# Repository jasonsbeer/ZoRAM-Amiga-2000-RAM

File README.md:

# ZoRAM - Eight Megabyte Fast RAM Expansion for the Amiga 2000

This project does not work at this time. Build at your own risk.

I have always felt big box Amiga's should be used as intended. Expansion should be targeted to the expansion slots provided. This project aims to provde an 8 megabyte expansion option via the Zorro II bus of the Amiga 2000. Based on LIV2's GottaGoFastRAM for 68000 DIP based Amigas. Due to the relative messiness of the  data and address line locations on the Zorro II connector, it was necessary to  change the connection points on the Xilinx. As such, the JED file for this project is specific to this project and cannot be interchanged with LIV2's original.

# PCB Ordering and Assembly

Under construction

# Programming the CPLD

To be completed later.

# BOM

|Component|Package|Location|QTY|Source|Part Number|
--- | --- | --- | --- | --- | ---
4Mx16 DRAM|TSOP(II)| U6 | 1 | Ali Express or E-Bay| K4E641612D or GM71VS65163
XC9572XL-10VQ64C|64-VQFP|U5|1|DigiKey|122-1266-ND or 122-1982-ND
AP2210N-3.3TRG1|SOT-23-3|U2|1|DigiKey|AP2210N-3.3TRG1DICT-ND
SN74LVC245A|SOIC|U3,U4|2|DigiKey|296-1232-1-ND
Ferrite Bead (600 Ohms@100MHz)|1206|FB1|1|DigiKey|MH3261-601YCT-ND
0.1uF Ceramic Capacitor|1206|C3-12|10|DigiKey|1276-2744-1-ND
4.7uF Ceramic Capacitor|1206|C1|1|DigiKey|1276-1055-1-ND
10uF Ceramic Capacitor|1206|C2|1|DigiKey|1276-1853-1-ND
6 Pin Male 2.54 Pitch Header (Optional)|--|J1|1|DigiKey|1849-PR20206VBNN-ND‎

# Revision History

V0.5 - Prototype Revision

V0.6 - Added missing trace between U3 pin 1 and U4 pin 1

V0.7 - Added ground planes

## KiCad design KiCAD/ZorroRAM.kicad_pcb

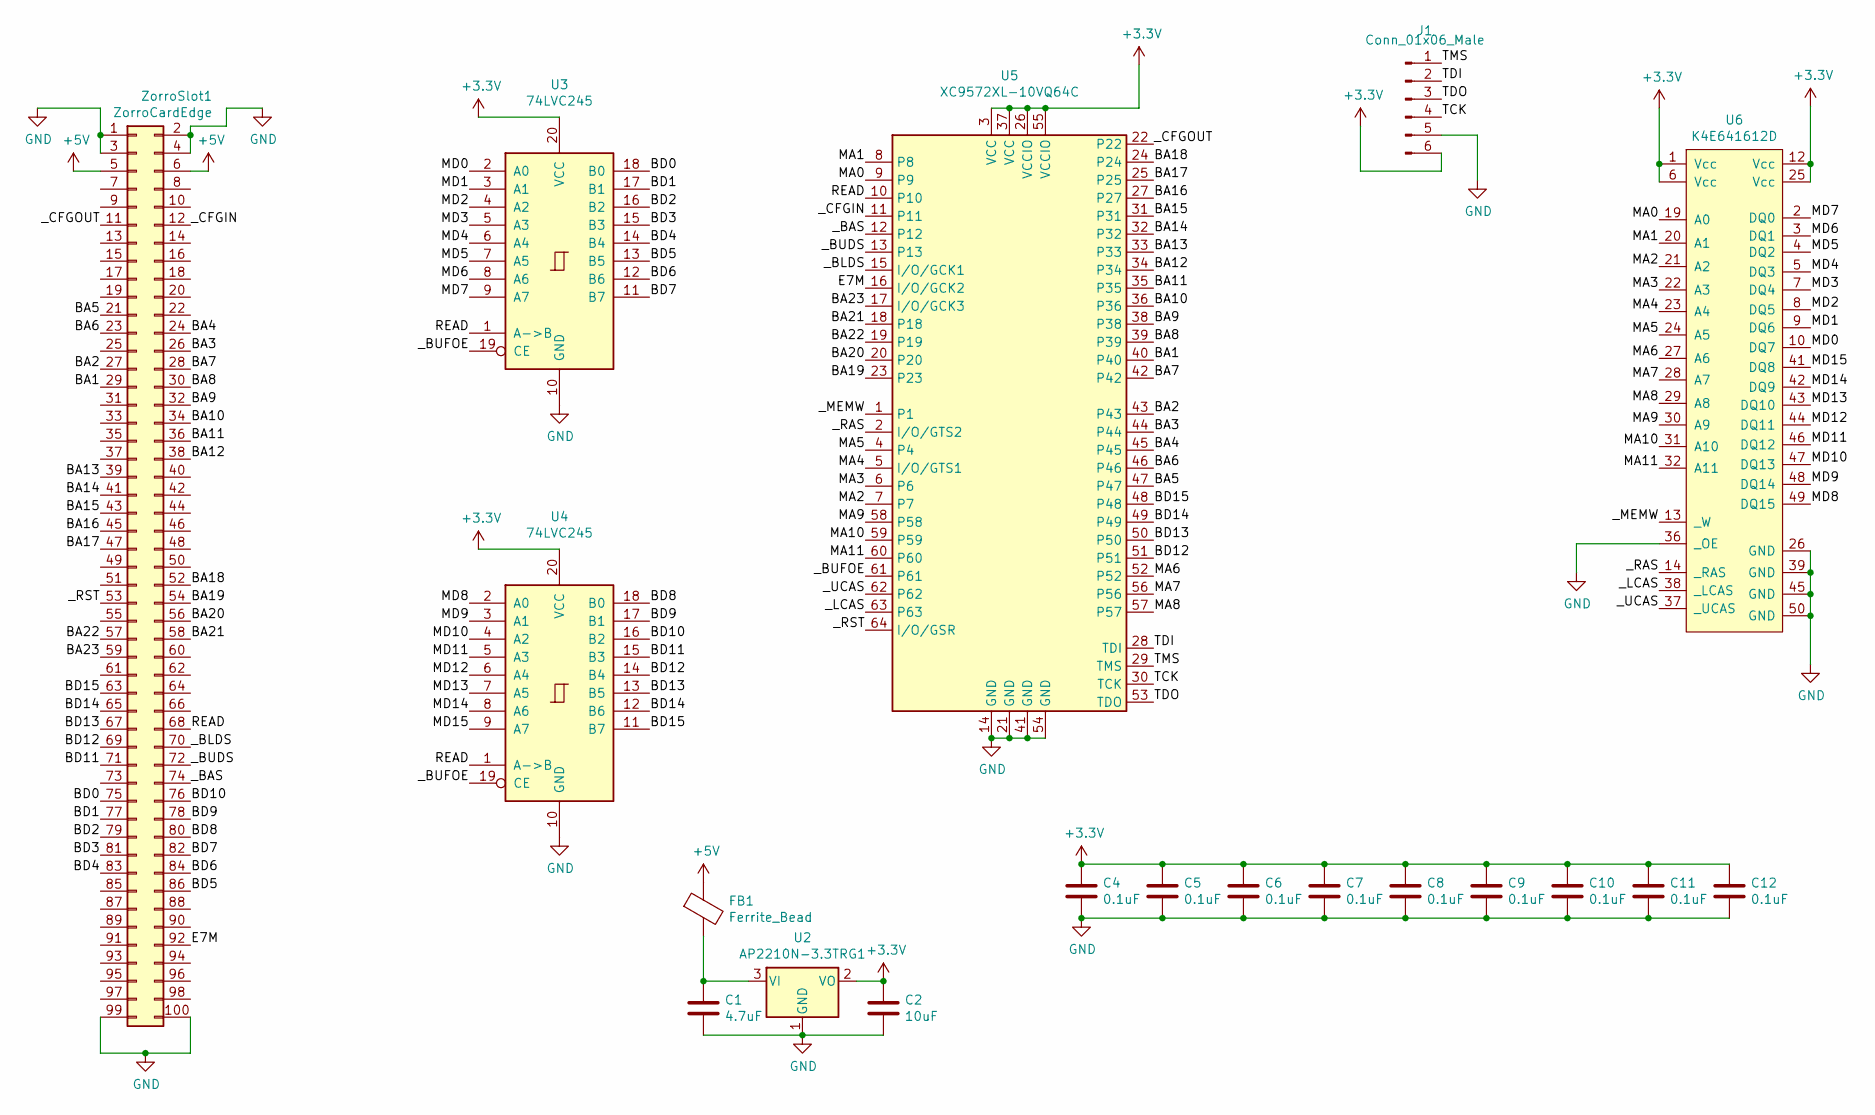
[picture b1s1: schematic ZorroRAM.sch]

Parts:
C1: 4.7uF; C_1206_3216Metric
C2: 10uF; C_1206_3216Metric
C4, C5, C6, C7, C8, C9, C10, C11, C12: 0.1uF; C_1206_3216Metric
FB1: Ferrite_Bead; C_1206_3216Metric
J1: Conn_01x06_Male; PinHeader_1x06_P2.54mm_Vertical
U2: AP2210N-3.3TRG1; SOT-23
U3, U4: 74LVC245; SOIC-20W_7.5x12.8mm_P1.27mm
U5: XC9572XL-10VQ64C; TQFP-64_10x10mm_P0.5mm
U6: K4E641612D; TSOP-II-50_P0.8mm
ZorroSlot1: ZorroCardEdge

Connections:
+3V3: C2.1, C4.1, C5.1, C6.1, C7.1, C8.1, C9.1, C10.1, C11.1, C12.1, J1.6, U2.2 (VO), U3.20 (VCC), U4.20 (VCC), U5.3 (VCC), U5.26 (VCCIO), U5.37 (VCC), U5.55 (VCCIO), U6.1 (Vcc), U6.6 (Vcc), U6.12 (Vcc), U6.25 (Vcc)
+5V: FB1.1, ZorroSlot1.5, ZorroSlot1.6
/BA1: U5.40, ZorroSlot1.29
/BA2: U5.43, ZorroSlot1.27
/BA3: U5.44, ZorroSlot1.26
/BA4: U5.45, ZorroSlot1.24
/BA5: U5.47, ZorroSlot1.21
/BA6: U5.46, ZorroSlot1.23
/BA7: U5.42, ZorroSlot1.28
/BA8: U5.39, ZorroSlot1.30
/BA9: U5.38, ZorroSlot1.32
/BA10: U5.36, ZorroSlot1.34
/BA11: U5.35, ZorroSlot1.36
/BA12: U5.34, ZorroSlot1.38
/BA13: U5.33, ZorroSlot1.39
/BA14: U5.32, ZorroSlot1.41
/BA15: U5.31, ZorroSlot1.43
/BA16: U5.27, ZorroSlot1.45
/BA17: U5.25, ZorroSlot1.47
/BA18: U5.24, ZorroSlot1.52
/BA19: U5.23, ZorroSlot1.54
/BA20: U5.20, ZorroSlot1.56
/BA21: U5.18, ZorroSlot1.58
/BA22: U5.19, ZorroSlot1.57
/BA23: U5.17 (I/O/GCK3), ZorroSlot1.59
/BD0: U3.18 (B0), ZorroSlot1.75
/BD1: U3.17 (B1), ZorroSlot1.77 (Pin77)
/BD2: U3.16 (B2), ZorroSlot1.79 (Pin79)
/BD3: U3.15 (B3), ZorroSlot1.81 (Pin81)
/BD4: U3.14 (B4), ZorroSlot1.83 (Pin83)
/BD5: U3.13 (B5), ZorroSlot1.86 (Pin86)
/BD6: U3.12 (B6), ZorroSlot1.84 (Pin84)
/BD7: U3.11 (B7), ZorroSlot1.82 (Pin82)
/BD8: U4.18 (B0), ZorroSlot1.80 (Pin80)
/BD9: U4.17 (B1), ZorroSlot1.78 (Pin78)
/BD10: U4.16 (B2), ZorroSlot1.76 (Pin76)
/BD11: U4.15 (B3), ZorroSlot1.71
/BD12: U4.14 (B4), U5.51, ZorroSlot1.69
/BD13: U4.13 (B5), U5.50, ZorroSlot1.67
/BD14: U4.12 (B6), U5.49, ZorroSlot1.65
/BD15: U4.11 (B7), U5.48, ZorroSlot1.63
/E7M: U5.16 (I/O/GCK2), ZorroSlot1.92 (Pin92)
/MA0: U5.9, U6.19 (A0)
/MA1: U5.8, U6.20 (A1)
/MA2: U5.7, U6.21 (A2)
/MA3: U5.6, U6.22 (A3)
/MA4: U5.5 (I/O/GTS1), U6.23 (A4)
/MA5: U5.4, U6.24 (A5)
/MA6: U5.52, U6.27 (A6)
/MA7: U5.56, U6.28 (A7)
/MA8: U5.57, U6.29 (A8)
/MA9: U5.58, U6.30 (A9)
/MA10: U5.59, U6.31 (A10)
/MA11: U5.60, U6.32 (A11)
/MD0: U3.2 (A0), U6.10 (DQ7)
/MD1: U3.3 (A1), U6.9 (DQ6)
/MD2: U3.4 (A2), U6.8 (DQ5)
/MD3: U3.5 (A3), U6.7 (DQ4)
/MD4: U3.6 (A4), U6.5 (DQ3)
/MD5: U3.7 (A5), U6.4 (DQ2)
/MD6: U3.8 (A6), U6.3 (DQ1)
/MD7: U3.9 (A7), U6.2 (DQ0)
/MD8: U4.2 (A0), U6.49 (DQ15)
/MD9: U4.3 (A1), U6.48 (DQ14)
/MD10: U4.4 (A2), U6.47 (DQ13)
/MD11: U4.5 (A3), U6.46 (DQ12)
/MD12: U4.6 (A4), U6.44 (DQ11)
/MD13: U4.7 (A5), U6.43 (DQ10)
/MD14: U4.8 (A6), U6.42 (DQ9)
/MD15: U4.9 (A7), U6.41 (DQ8)
/READ: U3.1 (A->B), U4.1 (A->B), U5.10, ZorroSlot1.68
/TCK: J1.4, U5.30 (TCK)
/TDI: J1.2, U5.28 (TDI)
/TDO: J1.3, U5.53 (TDO)
/TMS: J1.1, U5.29 (TMS)
/_BAS: U5.12, ZorroSlot1.74
/_BLDS: U5.15 (I/O/GCK1), ZorroSlot1.70
/_BUDS: U5.13, ZorroSlot1.72 (_BUDS)
/_BUFOE: U3.19 (CE), U4.19 (CE), U5.61
/_CFGIN: U5.11, ZorroSlot1.12
/_CFGOUT: U5.22, ZorroSlot1.11
/_LCAS: U5.63, U6.38 (_LCAS)
/_MEMW: U5.1, U6.13 (_W)
/_RAS: U5.2 (I/O/GTS2), U6.14 (_RAS)
/_RST: U5.64 (I/O/GSR), ZorroSlot1.53
/_UCAS: U5.62, U6.37 (_UCAS)
GND: C1.2, C2.2, C4.2, C5.2, C6.2, C7.2, C8.2, C9.2, C10.2, C11.2, C12.2, J1.5, U2.1 (GND), U3.10 (GND), U4.10 (GND), U5.14 (GND), U5.21 (GND), U5.41 (GND), U5.54 (GND), U6.26 (GND), U6.36 (_OE), U6.39 (GND), U6.45 (GND), U6.50 (GND), ZorroSlot1.1, ZorroSlot1.2, ZorroSlot1.3, ZorroSlot1.4, ZorroSlot1.99 (Pin99), ZorroSlot1.100 (Pin100)
unnamed: C1.1, FB1.2, U2.3 (VI)

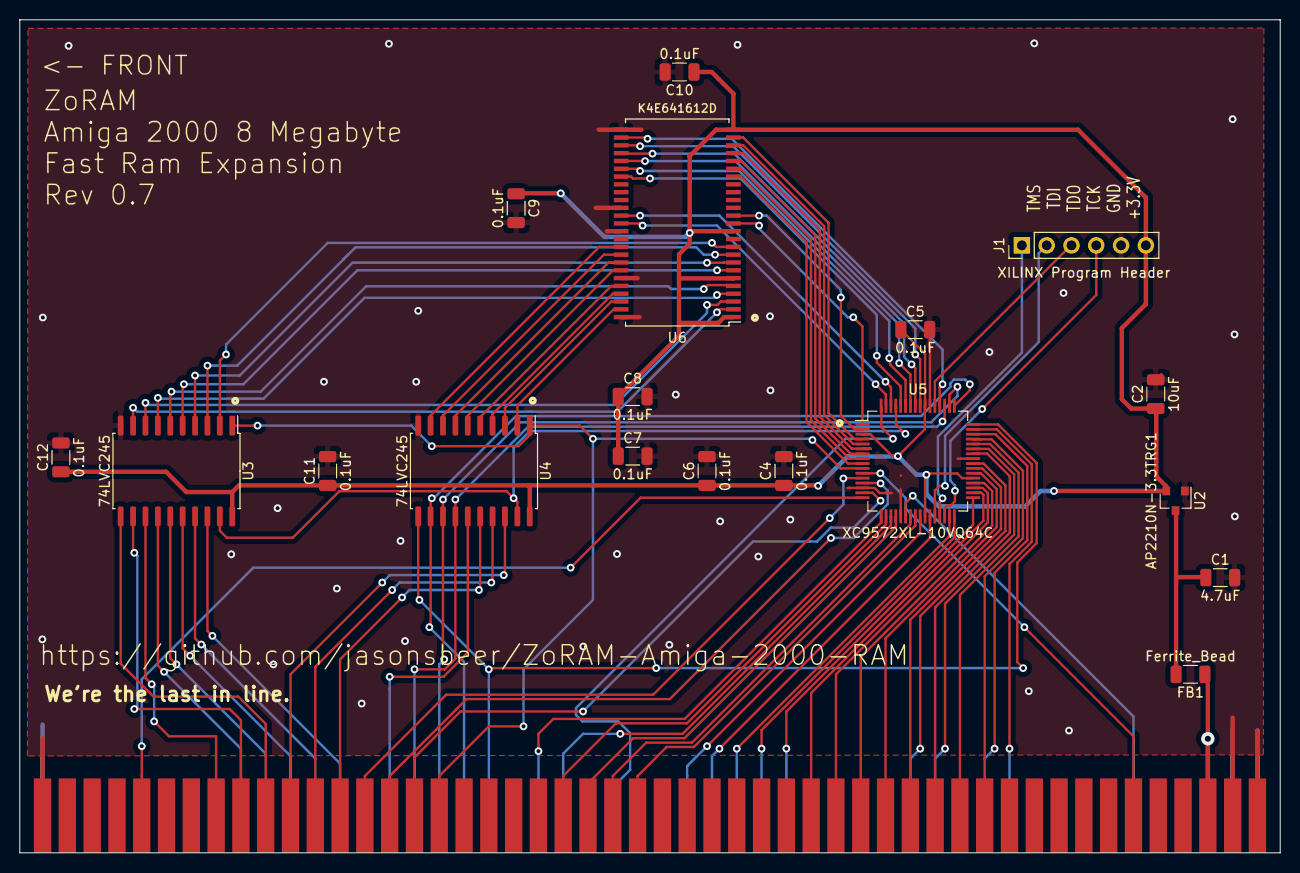
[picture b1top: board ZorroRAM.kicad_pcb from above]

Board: 2 copper layers, 129.1 x 85.3 mm, 19 parts (0 on the bottom side), 88 nets.
